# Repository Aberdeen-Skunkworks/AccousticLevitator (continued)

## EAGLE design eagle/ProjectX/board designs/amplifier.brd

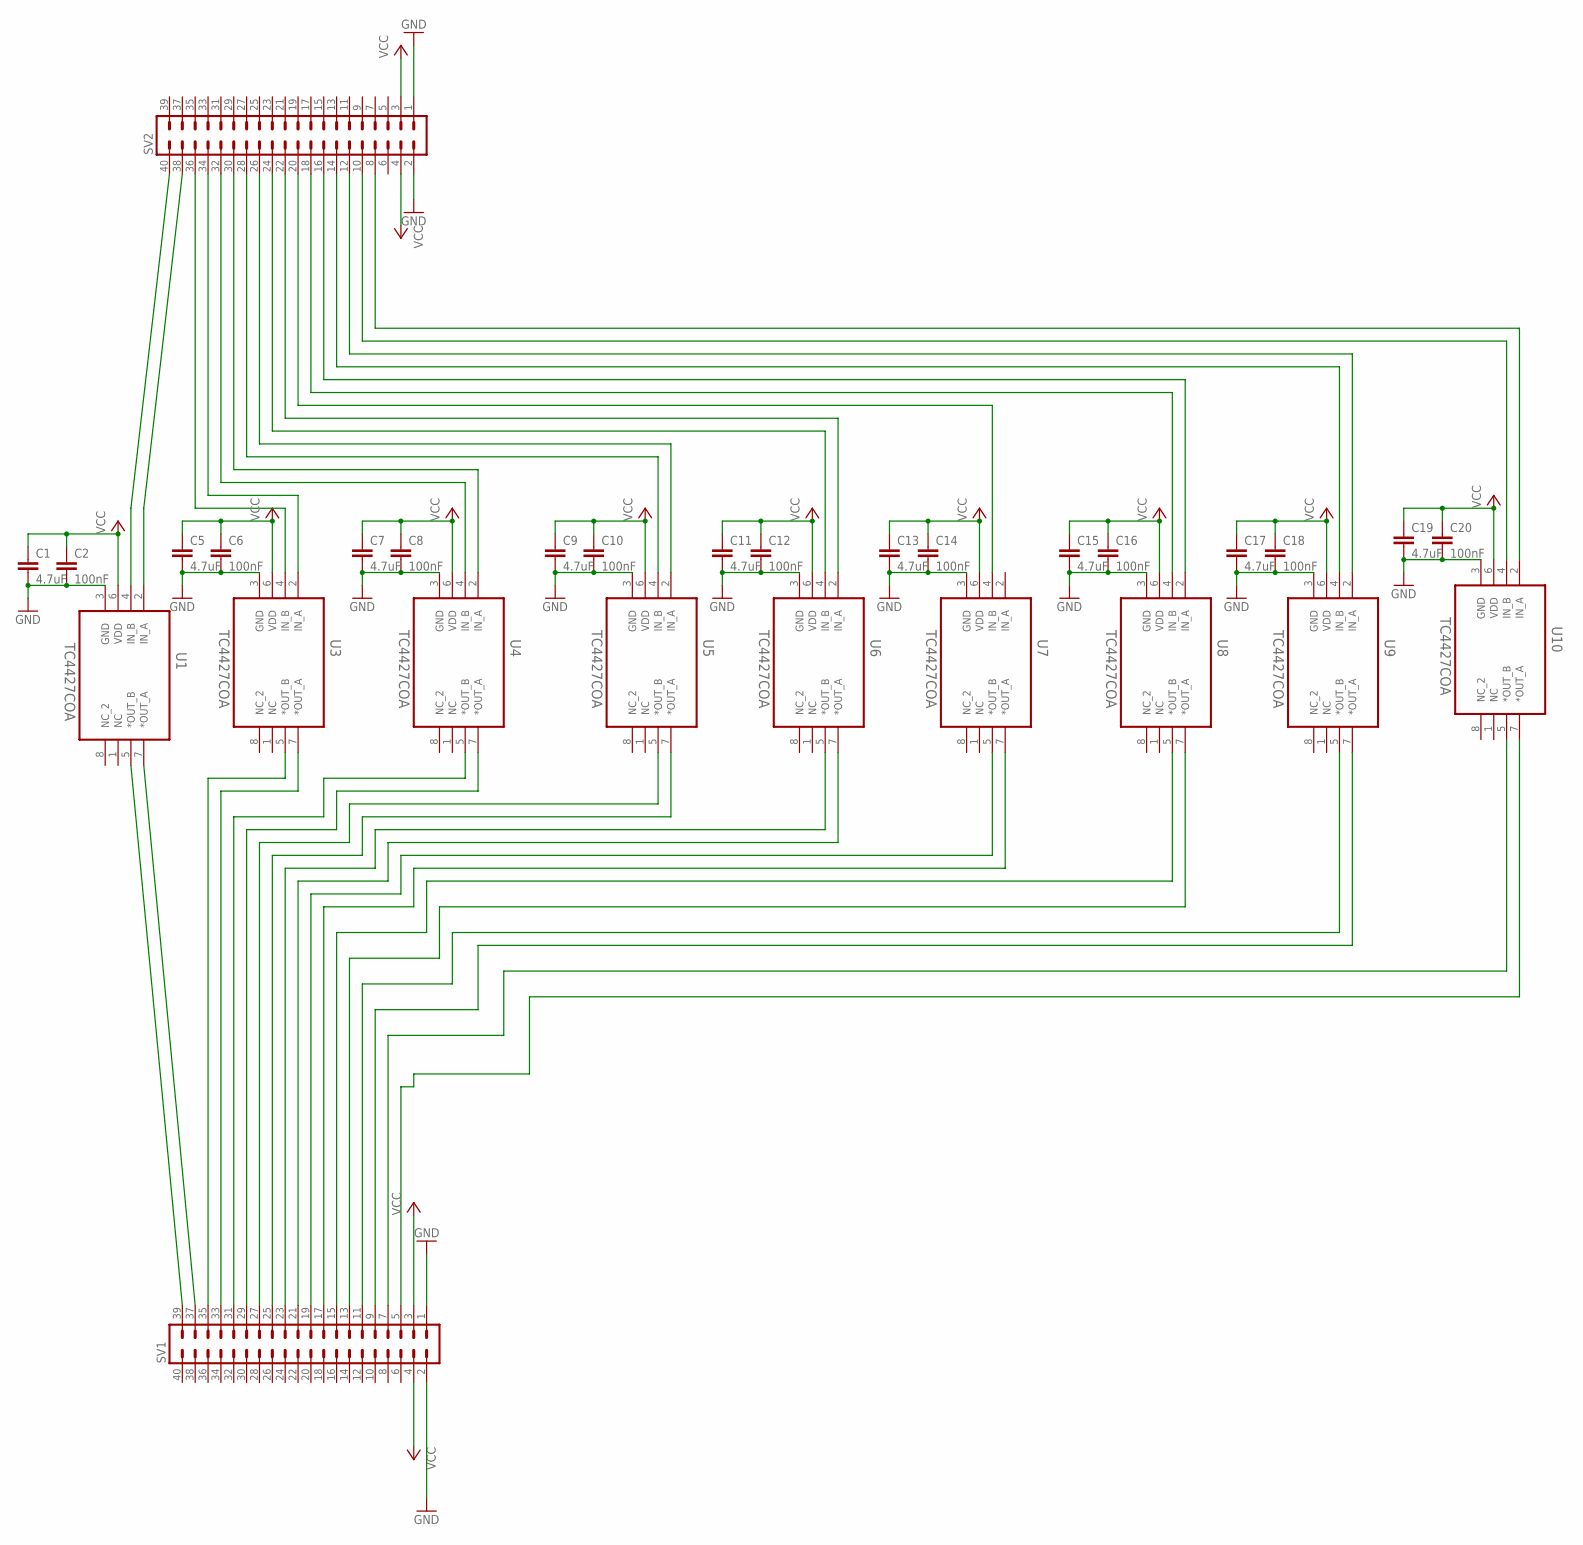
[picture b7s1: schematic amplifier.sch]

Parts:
C1, C5, C7, C9, C11, C13, C15, C17, C19: 4.7uF; C0805
C2, C6, C8, C10, C12, C14, C16, C18, C20: 100nF; C0805
SV1, SV2: MA20-2W
U1, U3, U4, U5, U6, U7, U8, U9, U10: TC4427COA; SOIC127P600X175-8N

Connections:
GND: C1.2, C2.2, C5.2, C6.2, C7.2, C8.2, C9.2, C10.2, C11.2, C12.2, C13.2, C14.2, C15.2, C16.2, C17.2, C18.2, C19.2, C20.2, SV1.1, SV1.2, SV2.1, SV2.2, U1.3 (GND), U3.3 (GND), U4.3 (GND), U5.3 (GND), U6.3 (GND), U7.3 (GND), U8.3 (GND), U9.3 (GND), U10.3 (GND)
unnamed: SV2.36, U3.4 (IN_B)
unnamed: SV1.39, U1.5 (*OUT_B)
unnamed: SV1.37, U1.7 (*OUT_A)
unnamed: SV2.40, U1.4 (IN_B)
unnamed: SV2.38, U1.2 (IN_A)
unnamed: SV2.34, U3.2 (IN_A)
unnamed: SV1.35, U3.5 (*OUT_B)
unnamed: SV1.33, U3.7 (*OUT_A)
unnamed: SV2.32, U4.4 (IN_B)
unnamed: SV2.30, U4.2 (IN_A)
unnamed: SV1.31, U4.5 (*OUT_B)
unnamed: SV1.29, U4.7 (*OUT_A)
unnamed: SV1.27, U5.5 (*OUT_B)
unnamed: SV1.25, U5.7 (*OUT_A)
unnamed: SV2.28, U5.4 (IN_B)
unnamed: SV2.26, U5.2 (IN_A)
unnamed: SV1.23, U6.5 (*OUT_B)
unnamed: SV1.21, U6.7 (*OUT_A)
unnamed: SV2.24, U6.4 (IN_B)
unnamed: SV2.22, U6.2 (IN_A)
unnamed: SV1.19, U7.5 (*OUT_B)
unnamed: SV1.17, U7.7 (*OUT_A)
unnamed: SV2.20, U7.4 (IN_B)
unnamed: SV1.15, U8.5 (*OUT_B)
unnamed: SV1.13, U8.7 (*OUT_A)
unnamed: SV2.18, U8.4 (IN_B)
unnamed: SV2.16, U8.2 (IN_A)
unnamed: SV2.14, U9.4 (IN_B)
unnamed: SV2.12, U9.2 (IN_A)
unnamed: SV1.11, U9.5 (*OUT_B)
unnamed: SV1.9, U9.7 (*OUT_A)
unnamed: SV2.10, U10.4 (IN_B)
unnamed: SV2.8, U10.2 (IN_A)
unnamed: SV1.5, U10.7 (*OUT_A)
unnamed: SV1.7, U10.5 (*OUT_B)
VCC: C1.1, C2.1, C5.1, C6.1, C7.1, C8.1, C9.1, C10.1, C11.1, C12.1, C13.1, C14.1, C15.1, C16.1, C17.1, C18.1, C19.1, C20.1, SV1.3, SV1.4, SV2.3, SV2.4, U1.6 (VDD), U3.6 (VDD), U4.6 (VDD), U5.6 (VDD), U6.6 (VDD), U7.6 (VDD), U8.6 (VDD), U9.6 (VDD), U10.6 (VDD)

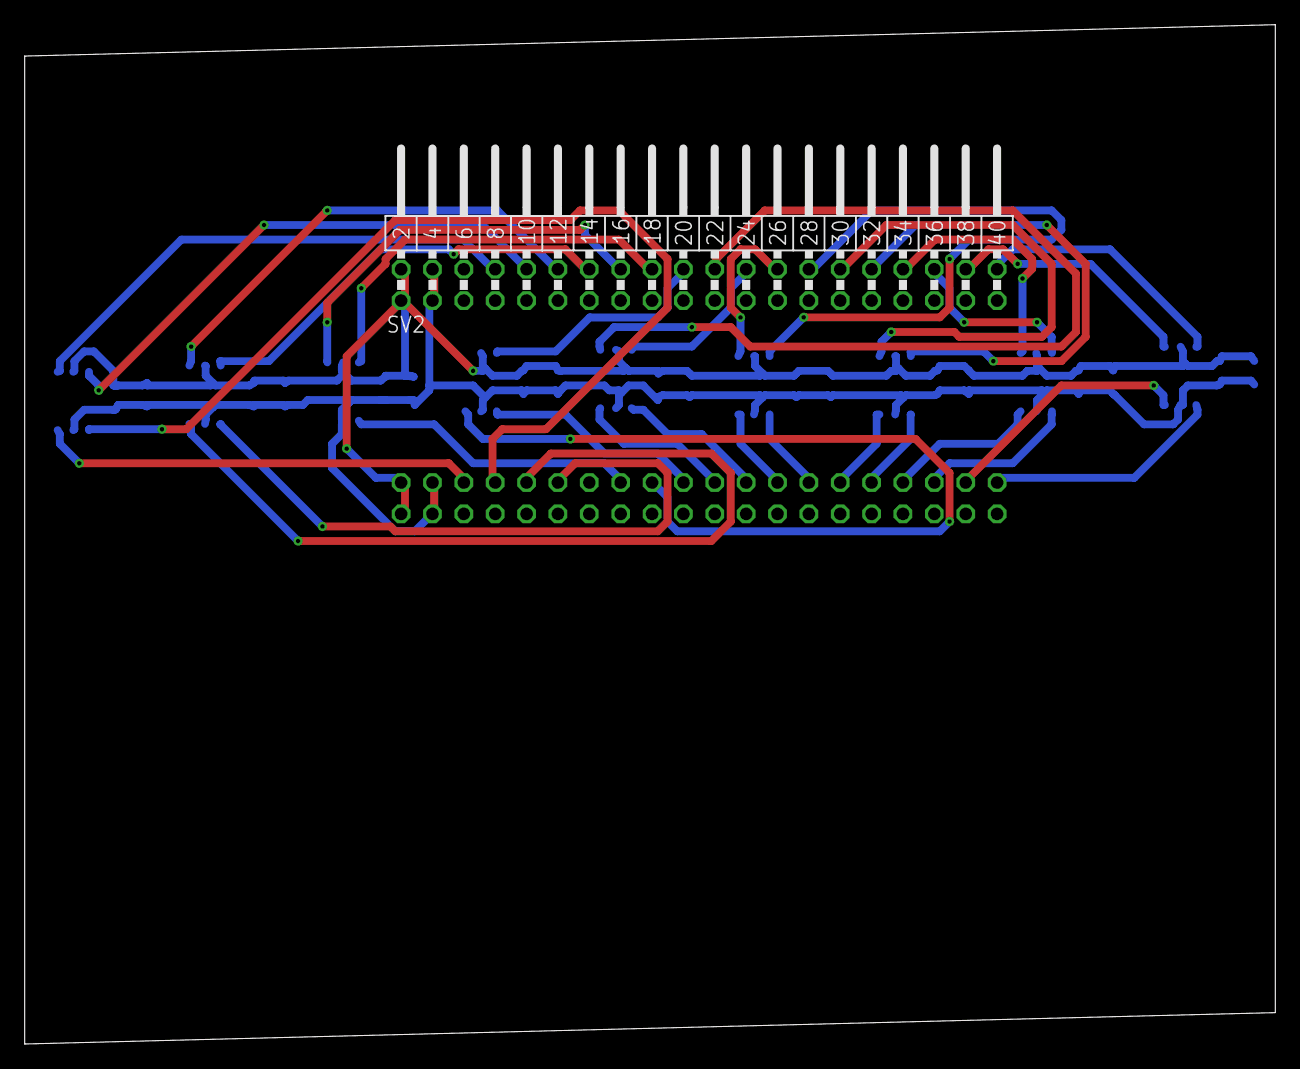
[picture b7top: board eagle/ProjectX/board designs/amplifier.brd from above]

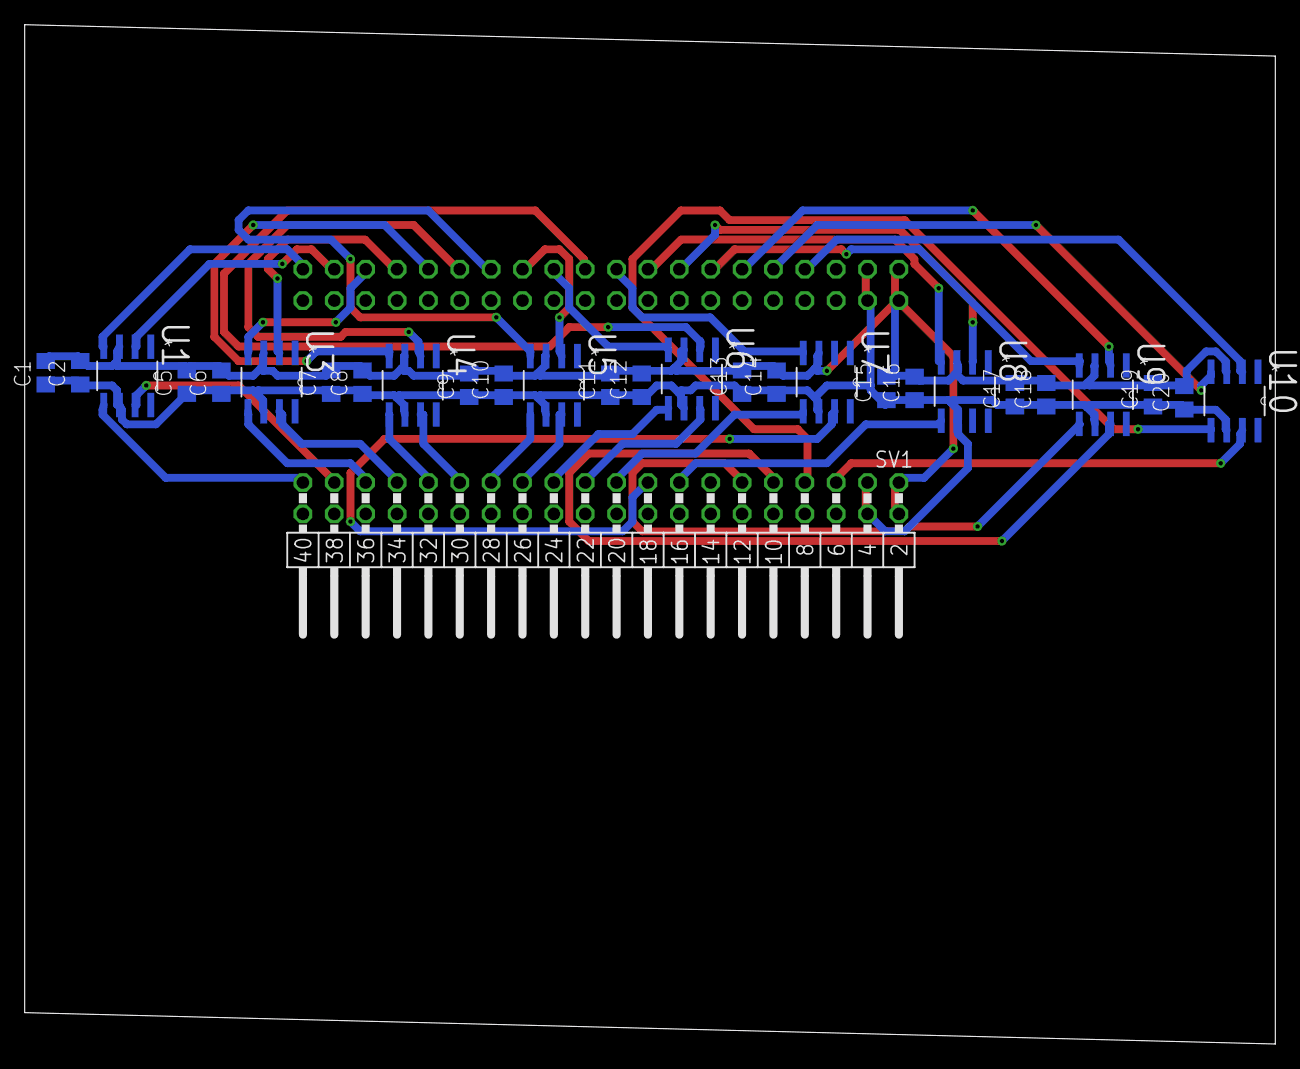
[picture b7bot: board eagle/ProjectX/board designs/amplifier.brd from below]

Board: 2 copper layers, 101.3 x 82.5 mm, 29 parts (28 on the bottom side), 37 nets.

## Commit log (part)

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2017-10-13 Upload of initial files to github
2017-10-13 added a new file to write vti files and editied that function out of main program
2017-10-13 Changed find phi to find the focus point phases instead of searching for a minimum (will add holographic traps next)
2017-10-14 Fixing equation typo in phifind (missing bracket) still check if equation needs to be divided by pi or not (comment in code)
2017-10-18 Condenced multiple similar functions into 1 file so they are easier to keep track of and use in the code. added the ability to search for the angle of a transducer on the xz plane looking from above 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
2017-10-18 Added Vortex Signature to phase algorithms
2017-10-18 Put particle diameter back to 5mm
2017-10-20 Added the FPGA files for the PWM unit
2017-10-20 Fixed potential energy of particle being the wrong sign (previously potential energy was going down with height which is wrong)
2017-10-20 Fixed freq to 40khz
2017-10-21 Set the counter width as a parameter and reduced it to 10 bits
2017-10-22 FPGA is working at 64 channels and can update the offsets at 220Hz, so everything appears to be satisfactory for the build
2017-10-23 Small changes to allow the 16 channel output test board
2017-10-24 Adding some eagle design parts
2017-10-26 Added the microchip library
2017-10-27 More work
2017-10-27 Fixed some errors in the sin_theta derrivation
2017-10-27 Finally got the analytical solution for the derivtive of the complex acoustic pressure
2017-10-27 Adding a function to calculate the analytical pressure derivatives into the algorithms file
2017-11-07 Some work on the final design
2017-11-07 More work on the 32 bit board
2017-11-07 Added a finished board
2017-11-17 old commit for calculating pressure
2017-11-17 Adding ability to delete transducers from the array to have any shape required and output that positions as co-ordinates to be used in the phase finding code
2017-11-17 Fixed bug where deletions cant be out of order
2017-11-19 Added function to delete transducers like the small 32 array so it can be simulated and added the ability to calculate circle co-ordinates as a start to 3d manipulation
2017-11-22 Added to the testing file the ability to save animations of sucsessive simulations and a circular example is included as proof of concept
2017-11-24 Some work on a transducer board
2017-11-24 Finished the 32 transducer board
2017-11-28 finished the FPGA package
2017-11-29 Fixed some errors in the FPGA package, and added a SMT variant for the big board
2017-11-29 Working on the SMT package
2017-11-30 Working on the big board
2017-11-30 Layout of transducers complete, need to add connectors, power, and then route everything
2017-11-30 Some fixes to placement
2017-12-01 More work on the board
2017-12-01 Routed 16 channels
2017-12-01 Netted up all the remaining amplifiers, need to route and net the FPGA pins to the amplifiers
2017-12-01 Still routing traces
2017-12-01 About 80% complete routing
2017-12-01 More work on routing
2017-12-03 Minor revision to add ground to the data port
2017-12-08 Slight improvements to the board, incase we need a new version in the future
2017-12-15 Older changes
2017-12-15 Restored the eagle work to the last working copy
2017-12-15 Reversed all of Nialls rampage through the circuit diagrams, also numbered the transducers in eagle so we can easily export positions
2017-12-15 Added the days updates of the FPGA code
2017-12-16 Added all 88 outputs on the UltraManip
2017-12-16 Fixed the circle co-ordinate algorithm
2017-12-16 Slight correction
2017-12-16 Adding the ability to import the large array, or any other set of positions from excel and ability to visulise the array layout and delete unwanted transducers
2017-12-16 Added the ability to produce a list of phase offsets as a list of ints from 0-1249 and the ability to export the gorkov potential as a vti image to view in paraview
2017-12-17 Fixes for running on windows
2017-12-17 Work from tryiing to get the board working
2017-12-17 Coppied the connect.py into the project x folder
2017-12-17 Some small tidy ups
2017-12-18 Fixed the error on the connect.py and removed the extra connect in the FPGA folder moved the running function to algorithms
2017-12-18 Moved the running board functions to a new file run_board and make the file easier to use with a selector to choose between haptic and pattern modes
2017-12-18 small changes
2017-12-19 corrected a wrong print
2018-01-09 Updating functions for analytical solution of the acoustic potential
2018-01-09 forgot a file
2018-01-10 Added ability to calculate the potential field analytically, this has revieled errors in the previous way this was calculated. This will need to be investigated. Algorithms currently holding the anal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
2018-01-11 Added diameter to circle function in -algorithms-
2018-01-11 Fixed problem wiht pressure calculation on top of a transducer and when the angle was 0.(may need looked into )
2018-01-12 Particle simulator sort of working (Needs work, visuliser needs more work, zero line look into?)
2018-01-12 Particle simulator in working state
2018-01-12 Verlet Algorithm added (testing still required)
2018-01-15 Particle simulation constatns problem fixed
2018-01-16 Added demo file that does haptics and basic trap
2018-01-19 GUI test file working
2018-01-20 GUI movment in progress and working in theory needs tweaked to work with board
2018-01-20 GUI improvments FUZZ mode added
2018-01-24 Small changes to files
2018-01-24 particle simulation changes and additions
2018-01-26 Adding the arduino controller
2018-01-28 Changes to main trying to de-bug the main clacluation of the fields
2018-01-28 small change to simulation
2018-01-28 Fixed assignment errors in the main file
2018-01-29 Chnages to the main code and to the twin signatures so it goes between different angles and not zero and pi
2018-01-29 Making the code faster with numpy
2018-01-29 Converting all the slow loops to numpy calculations to speed up the code (100 X faster calculations)
2018-01-30 Fixed Stupid mistake in twin signature where half the transducers were set back to zero .... duuuhh
2018-01-30 Small touch ups
2018-01-30 Changed to add discritisation to the phases
2018-01-30 Fixed conflicts
2018-01-30 Adding noise to the main function
2018-01-31 Starting to work on plotting phase contributions from each transducer
2018-02-07 Now have the Lolin32 lite board working as the USB uart, on to removing glitches
2018-02-08 Added a sync line
2018-02-08 Completely removed fuzzing
2018-02-09 I now have output power modulation working correctly, all FPGAs need reprogramming
2018-02-10 Added 3D vector plotter so that the transducer locations and directions can be visulised in 3D
2018-02-10 changed the co-ordinate system so z is up and fixed the inconsistencies with the co-ordinate system in python and in the parawiew files
2018-02-10 Added the ability to calcualte two opposing arrays(phase stuff needs work on them(something like a board function and board center))
2018-02-14 Some patches to the demo
2018-02-14 Working on audio file stuff
2018-02-15 changed to the demo and algorithms --fix needed on angle algorithm
2018-02-16 Forgot a +
2018-02-19 Working on plotting the forces on the particle
2018-02-19 Working on force particle force calculation and plottion
2018-02-21 Added new function of angle of twin signature so rotation is easy to implament (angle of plane set in degrees for ease of use)
2018-02-22 Working on potential energy, make sure gravity term makes sense (making the grid different sizes changes values)
2018-02-22 Fixed stuid error with taking the edge of the matrix instead of the middle!
2018-02-23 Working on particle simulation
2018-02-25 Changes for particle simulation
2018-02-26 Small changes to algorithms
2018-02-27 Added repetition of the commands to debug serial output
2018-02-27 Added version control
2018-02-27 All works, even with divisor modulation
2018-02-28 Small changes to constants
2018-03-01 Improved haptic mode
2018-03-01 Removed buzzer mode, as the haptic mode is really how this should be done now, also set the output DAC power to full (256) for other modes
2018-03-01 Working on finding out why all outputs are disabled
2018-03-01 Enabled external syncing
2018-03-01 Made the input for the demo more user friendly
2018-03-01 typo fixed
2018-03-02 Error in the volume calc
2018-03-02 Small chnaged to the force calc
2018-03-02 Working on particle sim (Wrong direction for gravity after convention change)
2018-03-04 Working on particle sim (Gravity too strong? units?)
2018-03-04 Particle sim work
2018-03-04 Changes to the particle sims
2018-03-06 Fixed the constants to match our real array
2018-03-06 Added initial 2d flood fill tests expand to 3d then take to trapping arrays
2018-03-06 3D flod fill works but recursion problems
2018-03-06 Flood fill with much less recursion
2018-03-06 2D version works now with changable itterations, Need to work on converting to 3D version
2018-03-09 3D fill sort of works needs to be checked
2018-03-10 Small changes to the fill and force calc stuff
2018-03-15 Added bottle and vortex signature
2018-03-16 Region filling start
2018-03-17 Region filling working better (Insane number of regions)
2018-03-18 Force calc now as a function in algorithms and flood fill region is working
2018-03-18 small changes to constatns
2018-03-20 Flood fill work
2018-03-21 finds all edge regions
2018-03-21 Work on fill not working at all
2018-03-22 working on the fill hiararicy
2018-03-23 Working 1d hiariarcy flood fill
2018-03-23 More work on flood fill
2018-03-23 Working tree flood fill in 1D and export to graph image
2018-03-24 3D working along with region dictionary and informationgit add -u! wooo
2018-03-25 More work on the flood filling thing
2018-03-26 Small changes to fill algorithm
2018-03-26 Added some comments to the min finding implamentation
2018-03-31 Added file to be able to change heights without editing the main file too much vti_writer had a typo that is fixed and the forces output now has the correct origin
2018-03-31 Polar directionality plotter finally rememberd to save a version of this
2018-04-12 Small changes to some constatns
2018-04-13 added version to calculate in a grid over the array
2018-05-21 Fixing typo
2018-05-25 Added the moddeling files including the metal profiles
2018-07-25 Focussing, trapping, and haptic feedback all working
2018-08-20 Demo working with new bords for p and h modes not focusing properly with the old code
2018-08-21 BAUD update
2018-08-21 Tried to set slew rate control, but this did not fix noise
2018-09-12 Adding Nialls board files
2018-09-13 Work in progress driver board
2018-09-16 Niall bord edits
2018-09-17 Niall Board layout first attempt
2018-09-18 Some work
2018-09-18 Nialls slightly better board atempt 2
2018-09-19 Now have a working gorkov calculator
2018-09-19 Added animations
2018-09-19 Fixed unit tests
2018-09-20 Nialls boards
2018-09-20 Nialls's boards
2018-09-21 Slight cleanup of the code
2018-09-22 Niall board edits
2018-09-22 Nialls board changes
2018-09-24 Niall's board work
2018-09-24 Niall board update
2018-09-25 Niall's amazing masterpeice
2018-09-26 Niall's board progress
2018-09-26 Niall more work
2018-09-28 Nialls board
2018-10-01 Niall board work
2018-10-02 Niall new board stuff
2018-10-05 Added transducer board
2018-10-05 Niall's board agagin
2018-10-06 Added capasitors to inputs
2018-10-06 Niall board more work
2018-10-07 More cleaning
2018-10-07 More DRC fixes, just about all done
2018-10-07 Tweak
2018-10-07 Bit more work
2018-10-07 fixed some issues on the driver
2018-10-07 Transievers routed
2018-10-08 More board work
2018-10-09 Niall board better wiring
2018-10-10 Fixed top right section of board
2018-10-10 Transducer board small changes
2018-10-10 Niall DRC errors fixed
2018-10-11 Niall almost done
2018-10-11 Transducer board in finished state
2018-10-12 New transducer numbering start
2018-10-12 Boards almost done
2018-10-12 Just spacing traces a little better if I can
2018-10-13 Version 0 Niall's boards finished design... maybe
2018-10-13 Finished driver board - maybe
2018-10-15 Finished board 1
2018-10-15 Added gerber files
2018-10-15 Transducer board tidied up a bit and submitted
2019-02-04 fixed error in tests (sys.potential -> sys.Gorkov_potential)
